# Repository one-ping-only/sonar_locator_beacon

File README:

# Locator beacon TX unit

Made with Kicad 7

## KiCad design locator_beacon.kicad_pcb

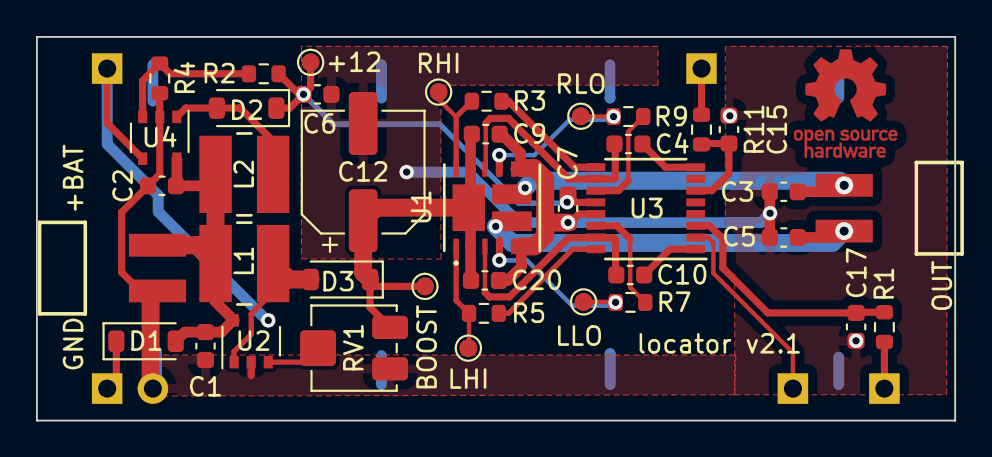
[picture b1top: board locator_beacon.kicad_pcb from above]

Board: 2 copper layers, 51.0 x 21.3 mm, 46 parts (1 on the bottom side), 27 nets.

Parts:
+12: +12; TestPoint_Pad_D1.0mm
C1, C2: C; C_0603_1608Metric
C3, C5: 220n; C_0603_1608Metric
C4, C6, C7, C9, C10, C20: 10u; C_0603_1608Metric
C12: C; CP_Elec_6.3x7.7
C15, C17: 1.5n; C_0603_1608Metric
D1, D2, D3: DSS16U; D_SOD-123
J1, J2: Conn_01x02; SAMTEC_TSM-102-01-L-SH
J3, J6, J7, J8: Conn_01x01; PinHeader_1x01_P2.54mm_Vertical
J4: OSHW logo; OSHW-Logo_5.7x6mm_Copper
J5: Conn_01x02; PinHeader_1x02_P2.54mm_Vertical
L1, L2: 10u; IND_357100_WRE
R1, R3, R5, R7, R9, R11: 2k; R_0603_1608Metric
R2: 42.3k; R_0603_1608Metric
R4: 5k; R_0603_1608Metric
RV1: 100k; Potentiometer_Bourns_3314J_Vertical
TP1: BOOST; TestPoint_Pad_D1.0mm
TP2: LHI; TestPoint_Pad_D1.0mm
TP4: LLO; TestPoint_Pad_D1.0mm
TP6: RLO; TestPoint_Pad_D1.0mm
TP7: RHI; TestPoint_Pad_D1.0mm
U1: DMHT6016LFJ-13; V-DFN5045-12_DIO
U2, U4: MIC2288; TSOP-5_1.65x3.05mm_P0.95mm
U3: MIC4606; TSSOP-16-1EP_4.4x5mm_P0.65mm
U13: Pico; RPi_pico

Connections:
+12V: +12.1, C6.1, C7.1, D2.1 (K), R2.1, U3.12 (VDD)
+BATT: C1.1, C2.1, D1.2 (A), J2.02, L1.1, L2.1, U2.5 (VIN), U4.5 (VIN)
/amplifier/EN: J3.1, U3.2 (EN), U13.24 (GPIO18)
/amplifier/L_HI: R5.1, TP2.1, U1.1 (G1)
/amplifier/L_LO: R7.1, TP4.1, U1.4 (G2)
/amplifier/OUT_A: C5.1, C10.2, J1.02, U1.3 (S1/D2), U1.14 (S1/D2), U3.15 (BHS)
/amplifier/OUT_B: C3.1, C4.2, J1.01, U1.10 (S4/D3), U1.15 (S4/D3), U3.10 (AHS)
/amplifier/R_HI: R3.1, TP7.1, U1.12 (G4)
/amplifier/R_LO: R9.1, TP6.1, U1.9 (G3)
/amplifier/SIG_IN: J7.1, R1.2, U13.22 (GPIO17)
/amplifier/~SIG_IN: J8.1, R11.2, U13.15 (GPIO11)
/power/EN: J6.1, U2.4 (EN), U4.4 (EN), U13.2 (GPIO1)
GND: C1.2, C2.2, C3.2, C5.2, C6.2, C7.2, C9.2, C12.2, C15.2, C17.2, C20.2, J2.01, J5.2, R4.2, RV1.3, U1.5 (S2), U1.6 (S2), U1.7 (S3), U1.8 (S3), U2.2 (GND), U3.13 (VSS), U4.2 (GND), U13.3 (GND), U13.8 (GND), U13.13 (GND), U13.18 (GND), U13.23 (GND), U13.28 (GND), U13.33 (AGND), U13.38 (GND)
unnamed: D1.1 (K), J5.1, U13.39 (VSYS)
unnamed: D2.2 (A), L2.2, U4.1 (SW)
unnamed: D3.2 (A), L1.2, U2.1 (SW)
unnamed: RV1.2, U2.3 (FB)
unnamed: C4.1, U3.8 (AHB)
unnamed: R3.2, U3.9 (AHO)
unnamed: R9.2, U3.11 (ALO)
unnamed: C15.1, R11.1, U3.6 (APWM)
unnamed: C10.1, U3.1 (BHB)
unnamed: R5.2, U3.16 (BHO)
unnamed: R7.2, U3.14 (BLO)
unnamed: C17.1, R1.1, U3.3 (BPWM)
unnamed: R2.2, R4.1, U4.3 (FB)
V_{boost}: C9.1, C12.1, C20.1, D3.1 (K), RV1.1, TP1.1, U1.2 (D1/D4), U1.11 (D1/D4), U1.13 (D1/D4)

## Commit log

2023-06-02 Add boost IC
2023-06-08 First production prototype
2023-06-11 Prod 1a
2023-07-01 Work
2023-07-01 Forgot to save
2023-08-01 Basic Class D amp
2023-10-03 Seems reasonable
2023-10-03 Adds license
2023-10-14 Tweaks
2023-11-01 Larger trace
2023-12-31 Stuff
2024-01-11 Shrunkified
2024-01-19 Separate +12 and boost
